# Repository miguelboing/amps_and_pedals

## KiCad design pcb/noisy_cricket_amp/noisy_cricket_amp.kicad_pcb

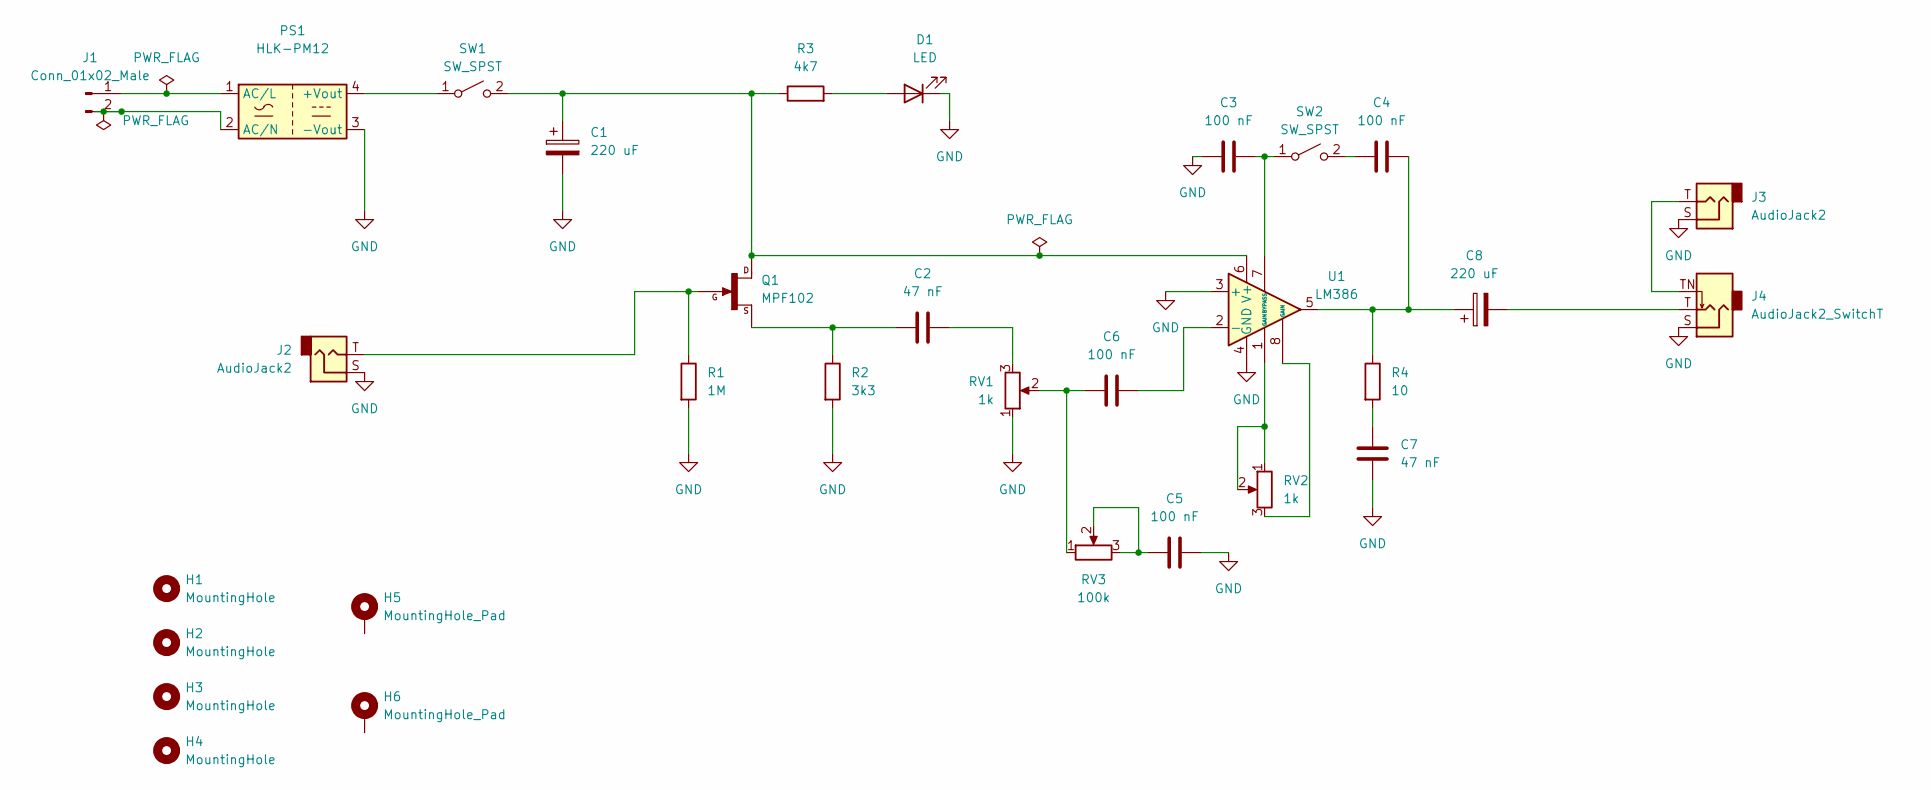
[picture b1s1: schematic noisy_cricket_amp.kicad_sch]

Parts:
C1, C8: 220 uF; CP_Radial_Tantal_D8.0mm_P5.00mm
C2, C7: 47 nF; C_Rect_L7.0mm_W2.0mm_P5.00mm
C3, C4, C5, C6: 100 nF; C_Rect_L7.0mm_W2.0mm_P5.00mm
D1: LED; LED_D3.0mm
H1, H2, H3, H4: MountingHole; MountingHole_2.2mm_M2
H5, H6: MountingHole_Pad; MountingHole_2.1mm
J1: Conn_01x02_Male; SolderWire-0.5sqmm_1x02_P4.8mm_D0.9mm_OD2.3mm
J2, J3: AudioJack2; SolderWire-0.5sqmm_1x02_P4.8mm_D0.9mm_OD2.3mm
J4: AudioJack2_SwitchT; SolderWire-0.5sqmm_1x03_P4.8mm_D0.9mm_OD2.3mm
PS1: HLK-PM12; Converter_ACDC_HiLink_HLK-PMxx
Q1: MPF102; TO92F
R1: 1M; R_Box_L8.4mm_W2.5mm_P5.08mm
R2: 3k3; R_Box_L8.4mm_W2.5mm_P5.08mm
R3: 4k7; R_Box_L8.4mm_W2.5mm_P5.08mm
R4: 10; R_Box_L8.4mm_W2.5mm_P5.08mm
RV1, RV2: 1k; Potentiometer_Vishay_T73XW_Horizontal
RV3: 100k; Potentiometer_Vishay_T73XW_Horizontal
SW1, SW2: SW_SPST; SolderWire-0.5sqmm_1x02_P4.8mm_D0.9mm_OD2.3mm
U1: LM386; DIL08

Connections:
GND: C1.2, C3.2, C5.2, C7.2, D1.1 (K), J2.S, J3.S, J4.S, PS1.3 (-Vout), R1.2, R2.2, RV1.1, U1.3 (+), U1.4 (GND)
unnamed: C1.1, Q1.1, R3.1, SW1.2 (B), U1.6 (V+)
unnamed: C2.1, RV1.3
unnamed: C2.2, Q1.2, R2.1
unnamed: C3.1, SW2.1 (A), U1.7 (BYPASS)
unnamed: C4.1, SW2.2 (B)
unnamed: C4.2, C8.1, R4.1, U1.5
unnamed: C5.1, RV3.2, RV3.3
unnamed: C6.1, U1.2 (-)
unnamed: C6.2, RV1.2, RV3.1
unnamed: C7.1, R4.2
unnamed: C8.2, J4.T
unnamed: D1.2 (A), R3.2
unnamed: J1.1, PS1.1 (AC/L)
unnamed: J1.2, PS1.2 (AC/N)
unnamed: J2.T, Q1.3, R1.1
unnamed: J3.T, J4.TN
unnamed: PS1.4 (+Vout), SW1.1 (A)
unnamed: RV2.1, RV2.2, U1.1 (GAIN)
unnamed: RV2.3, U1.8 (GAIN)

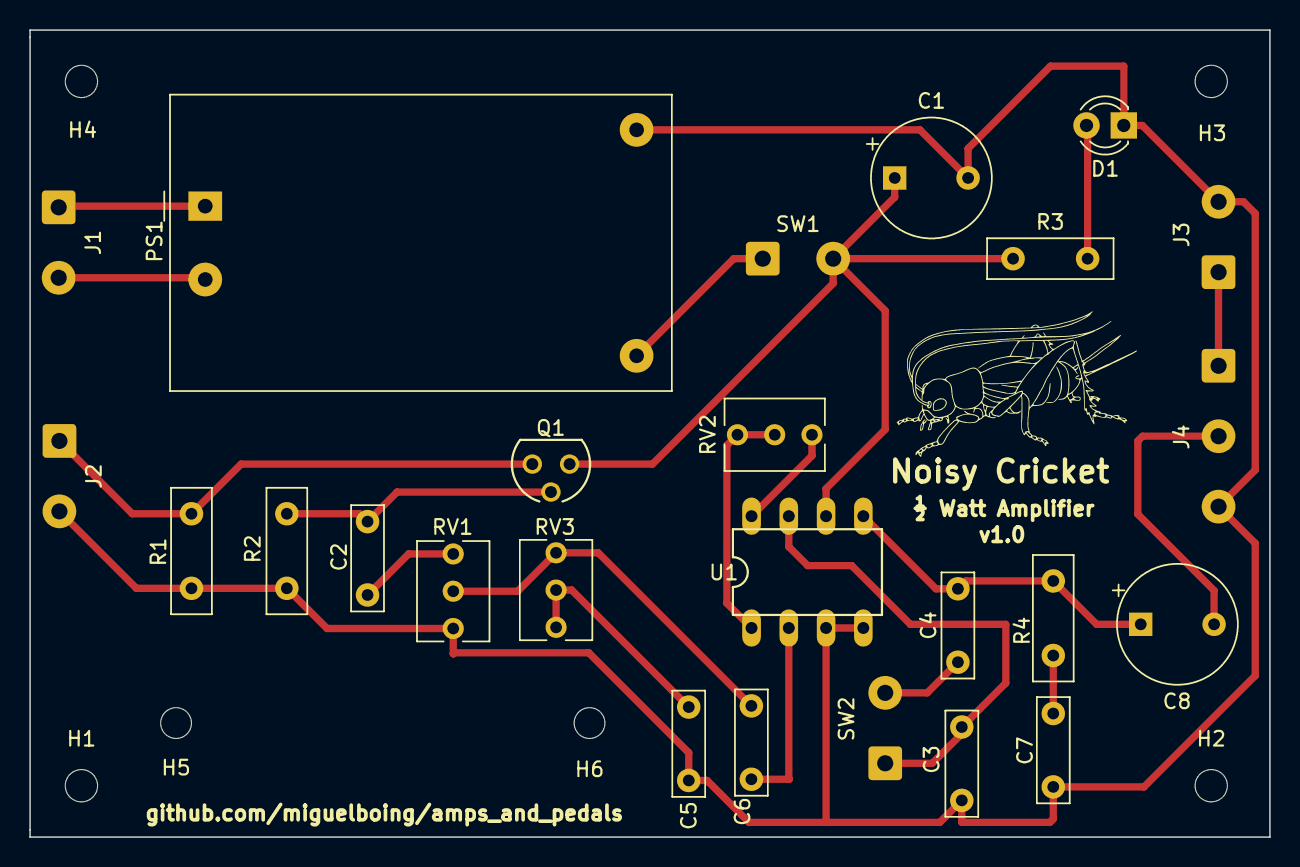
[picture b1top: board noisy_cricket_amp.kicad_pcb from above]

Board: 2 copper layers, 84.5 x 55.0 mm, 31 parts (0 on the bottom side), 20 nets.

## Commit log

2022-09-08 Initial pcb project
2022-10-14 Adding initial schematics
2022-11-10 Adding LM386 footprint
2022-11-10 Adding component footprints
2022-11-11 Initial pcb placement
2022-11-11 Creating .gitignore file
2023-02-04 Adding p10 output connector and initial pcb placement
2023-02-04 Routing component trails
2023-05-22 Adding cricket silk logo
2023-05-22 Importing AC-DC converter
2023-05-22 Holes for battery and layout improvements
